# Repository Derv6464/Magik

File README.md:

# Magik - Flight Computer

This was built as a final year project for college, as well as to create a flight computer for ULAS HiPR.
The code and pcb are rough drafts with work to be done before the first flight. 

## Hardware
The code & pcb were created with a rp2040 chip in mind

## Report
Full report can be veiwed in the repo

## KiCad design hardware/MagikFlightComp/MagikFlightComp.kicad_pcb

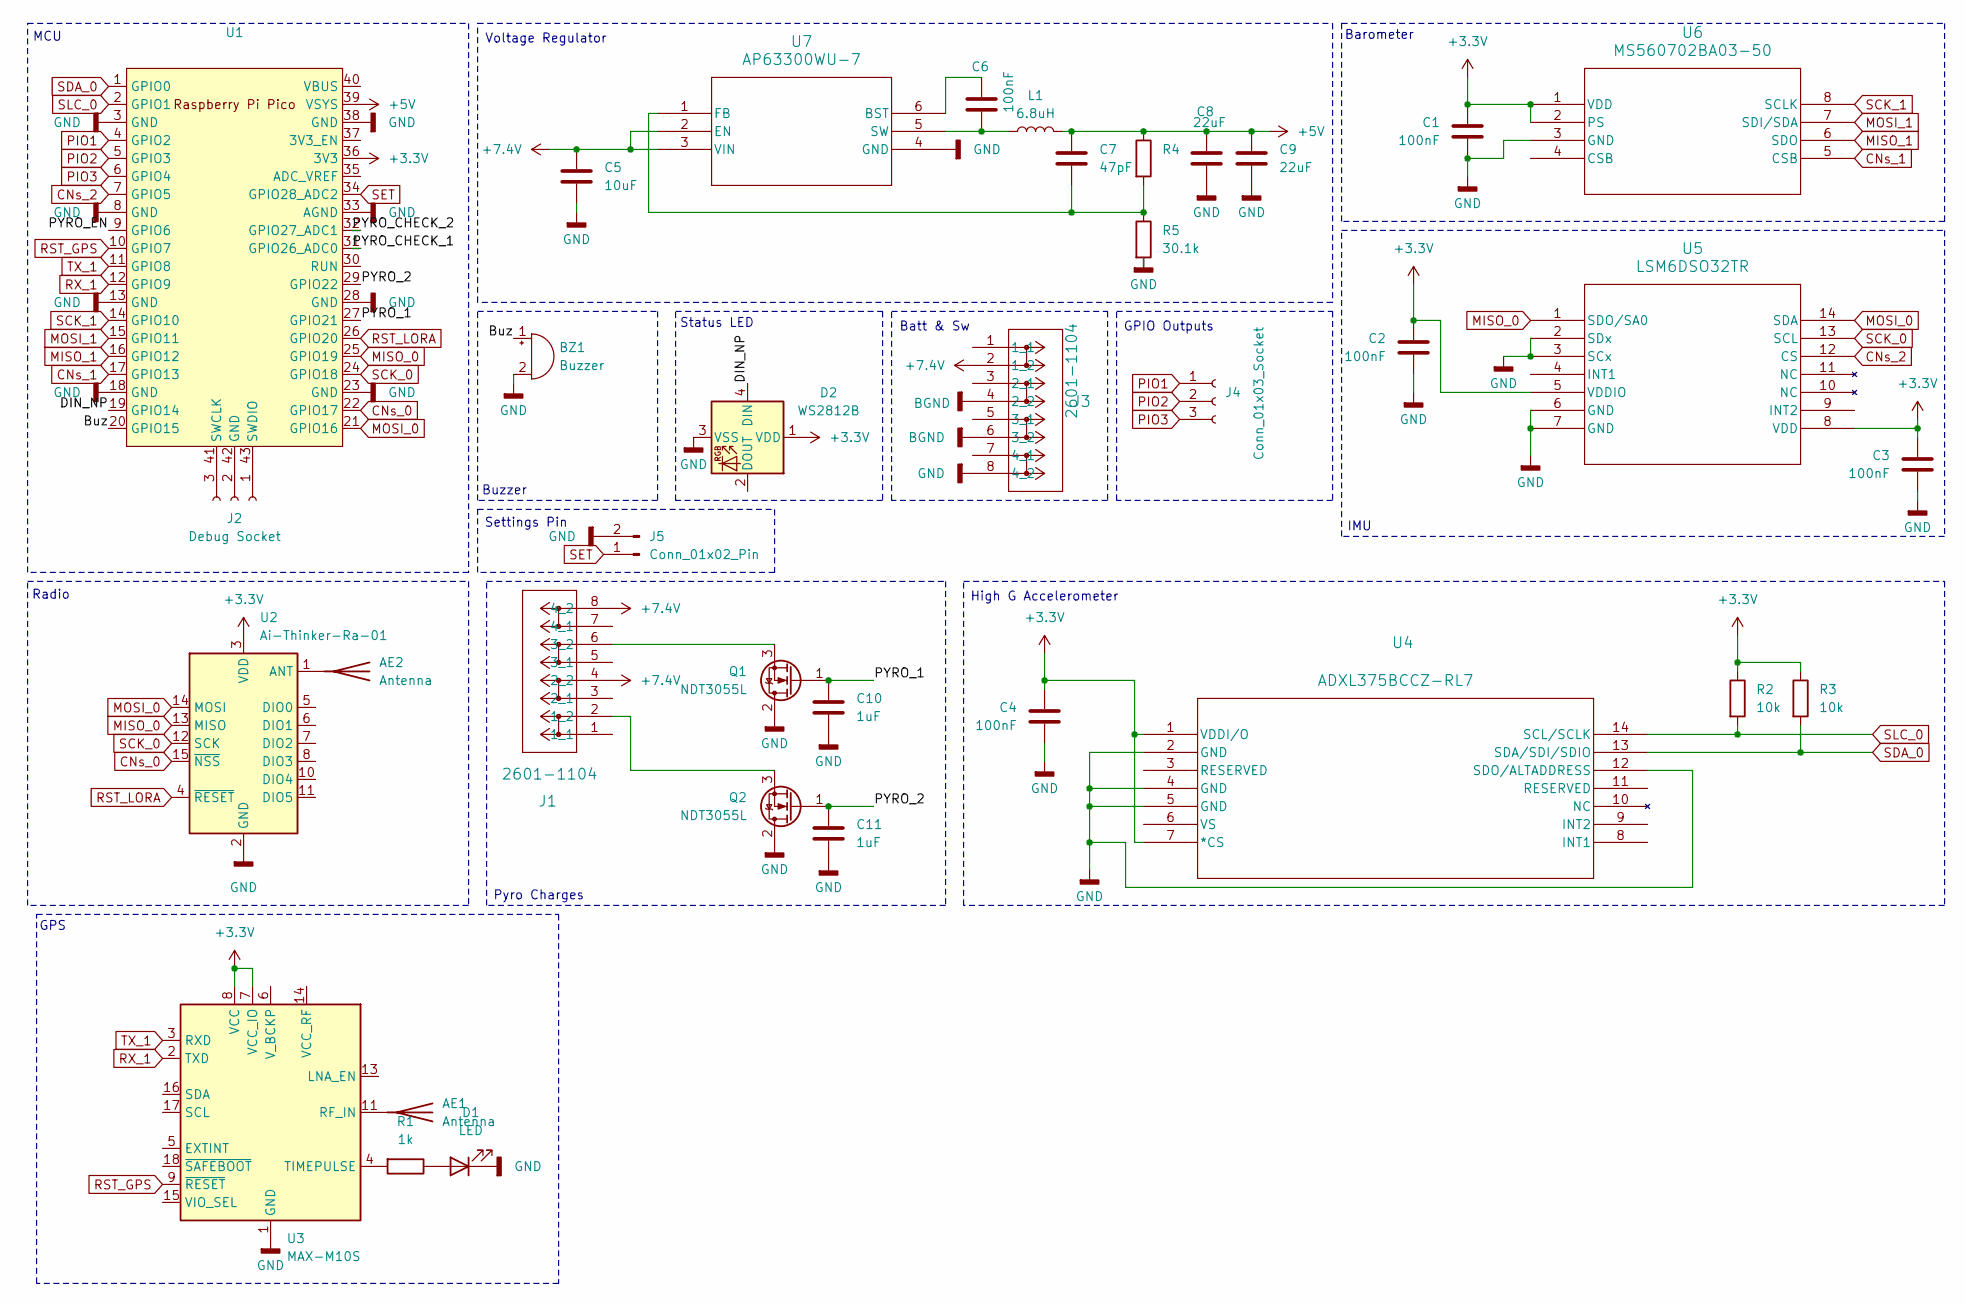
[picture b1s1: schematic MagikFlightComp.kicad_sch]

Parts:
AE1: Antenna
AE2: Antenna; SMA_Molex_73251-1153_EdgeMount_Horizontal
BZ1: Buzzer; Buzzer_12x9.5RM7.6
C1, C2, C3, C4, C6: 100nF; C_0603_1608Metric_Pad1.08x0.95mm_HandSolder
C5: 10uF; C_0603_1608Metric_Pad1.08x0.95mm_HandSolder
C7: 47pF; C_0603_1608Metric_Pad1.08x0.95mm_HandSolder
C8, C9: 22uF; C_0603_1608Metric_Pad1.08x0.95mm_HandSolder
C10, C11: 1uF; C_0603_1608Metric_Pad1.08x0.95mm_HandSolder
D1: LED; LED_1210_3225Metric
D2: WS2812B; LED_WS2812B_PLCC4_5.0x5.0mm_P3.2mm
J1, J3: 2601-1104; CONN4_2601-1104_WAG
J2: Debug Socket
J4: Conn_01x03_Socket; JST_PH_B3B-PH-K_1x03_P2.00mm_Vertical
J5: Conn_01x02_Pin; PinHeader_1x02_P1.00mm_Vertical
L1: 6.8uH; L_0603_1608Metric_Pad1.05x0.95mm_HandSolder
Q1, Q2: NDT3055L; SOT-223-3_TabPin2
R1: 1k; R_0603_1608Metric_Pad0.98x0.95mm_HandSolder
R2, R3: 10k; R_0603_1608Metric_Pad0.98x0.95mm_HandSolder
R4: 158k; R_0603_1608Metric_Pad0.98x0.95mm_HandSolder
R5: 30.1k; R_0603_1608Metric_Pad0.98x0.95mm_HandSolder
U1: Pico; RaspberryPi_Pico_W_SMD_HandSolder
U2: Ai-Thinker-Ra-01; Ai-Thinker-Ra-01-LoRa
U3: MAX-M10S; ublox_MAX
U4: ADXL375BCCZ-RL7; LGA_CC-14-1_ADI
U5: LSM6DSO32TR; LGA-14L_2P5X3X0P83_STM
U6: MS560702BA03-50; SON8_MS5611_TEC
U7: AP63300WU-7; TSOT6_AP63300WU-7_DIO

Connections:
+3.3V: C1.1, C2.1, C3.1, C4.1, D2.1 (VDD), R2.1, R3.1, U1.36 (3V3), U2.3 (VDD), U3.7 (VCC_IO), U3.8 (VCC), U4.1 (VDDI/O), U4.7 (*CS), U5.5 (VDDIO), U5.8 (VDD), U6.1 (VDD), U6.2 (PS)
+5V: C7.1, C8.1, C9.1, L1.2, R4.1, U1.39 (VSYS)
+7.4V: C5.1, J1.4 (2_2), J1.8 (4_2), J3.2 (1_2), U7.2 (EN), U7.3 (VIN)
/Buz: BZ1.1 (+), U1.20 (GPIO15)
/DIN_NP: D2.4 (DIN), U1.19 (GPIO14)
/PYRO_1: C10.1, Q1.1 (G), U1.27 (GPIO21)
/PYRO_2: C11.1, Q2.1 (G), U1.29 (GPIO22)
/PYRO_CHECK_1: U1.31 (GPIO26_ADC0)
/PYRO_CHECK_2: U1.32 (GPIO27_ADC1)
/PYRO_EN: U1.9 (GPIO6)
BGND: J3.4 (2_2), J3.6 (3_2)
CNs_0: U1.22 (GPIO17), U2.15 (~NSS)
CNs_1: U1.17 (GPIO13), U6.5 (CSB)
CNs_2: U1.7 (GPIO5), U5.12 (CS)
GND: BZ1.2 (-), C1.2, C2.2, C3.2, C4.2, C5.2, C8.2, C9.2, C10.2, C11.2, D1.1 (K), D2.3 (VSS), J3.8 (4_2), J5.2, Q1.2 (D), Q2.2 (D), R5.2, U1.3 (GND), U1.8 (GND), U1.13 (GND), U1.18 (GND), U1.23 (GND), U1.28 (GND), U1.33 (AGND), U1.38 (GND), U2.2 (GND), U2.9 (GND), U2.16 (GND), U3.1 (GND), U3.10 (GND), U3.12 (GND), U4.2 (GND), U4.4 (GND), U4.5 (GND), U4.12 (SDO/ALTADDRESS), U5.2 (SDx), U5.3 (SCx), U5.6 (GND), U5.7 (GND), U6.3 (GND), U7.4 (GND)
MISO_0: U1.25 (GPIO19), U2.13 (MISO), U5.1 (SDO/SA0)
MISO_1: U1.16 (GPIO12), U6.6 (SDO)
MOSI_0: U1.21 (GPIO16), U2.14 (MOSI), U5.14 (SDA)
MOSI_1: U1.15 (GPIO11), U6.7 (SDI/SDA)
unnamed: AE1.1, U3.11 (RF_IN)
unnamed: AE2.1 (A), U2.1 (ANT)
unnamed: D1.2 (A), R1.1
unnamed: J1.2 (1_2), Q2.3 (S)
unnamed: J1.6 (3_2), Q1.3 (S)
unnamed: J2.1, U1.43 (SWDIO)
unnamed: J2.2, U1.42 (GND)
unnamed: J2.3, U1.41 (SWCLK)
unnamed: R1.2, U3.4 (TIMEPULSE)
unnamed: C6.1, U7.6 (BST)
unnamed: C7.2, R4.2, R5.1, U7.1 (FB)
unnamed: C6.2, L1.1, U7.5 (SW)
PIO1: J4.1, U1.4 (GPIO2)
PIO2: J4.2, U1.5 (GPIO3)
PIO3: J4.3, U1.6 (GPIO4)
RST_GPS: U1.10 (GPIO7), U3.9 (~RESET)
RST_LORA: U1.26 (GPIO20), U2.4 (~RESET)
RX_1: U1.12 (GPIO9), U3.2 (TXD)
SCK_0: U1.24 (GPIO18), U2.12 (SCK), U5.13 (SCL)
SCK_1: U1.14 (GPIO10), U6.8 (SCLK)
SDA_0: R3.2, U1.1 (GPIO0), U4.13 (SDA/SDI/SDIO)
SET: J5.1, U1.34 (GPIO28_ADC2)
SLC_0: R2.2, U1.2 (GPIO1), U4.14 (SCL/SCLK)
TX_1: U1.11 (GPIO8), U3.3 (RXD)

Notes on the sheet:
Radio
Buzzer
Settings Pin
High G Accelerometer
Voltage Regulator
GPS
MCU
Status LED
IMU
Batt & Sw
GPIO Outputs
Pyro Charges
Barometer

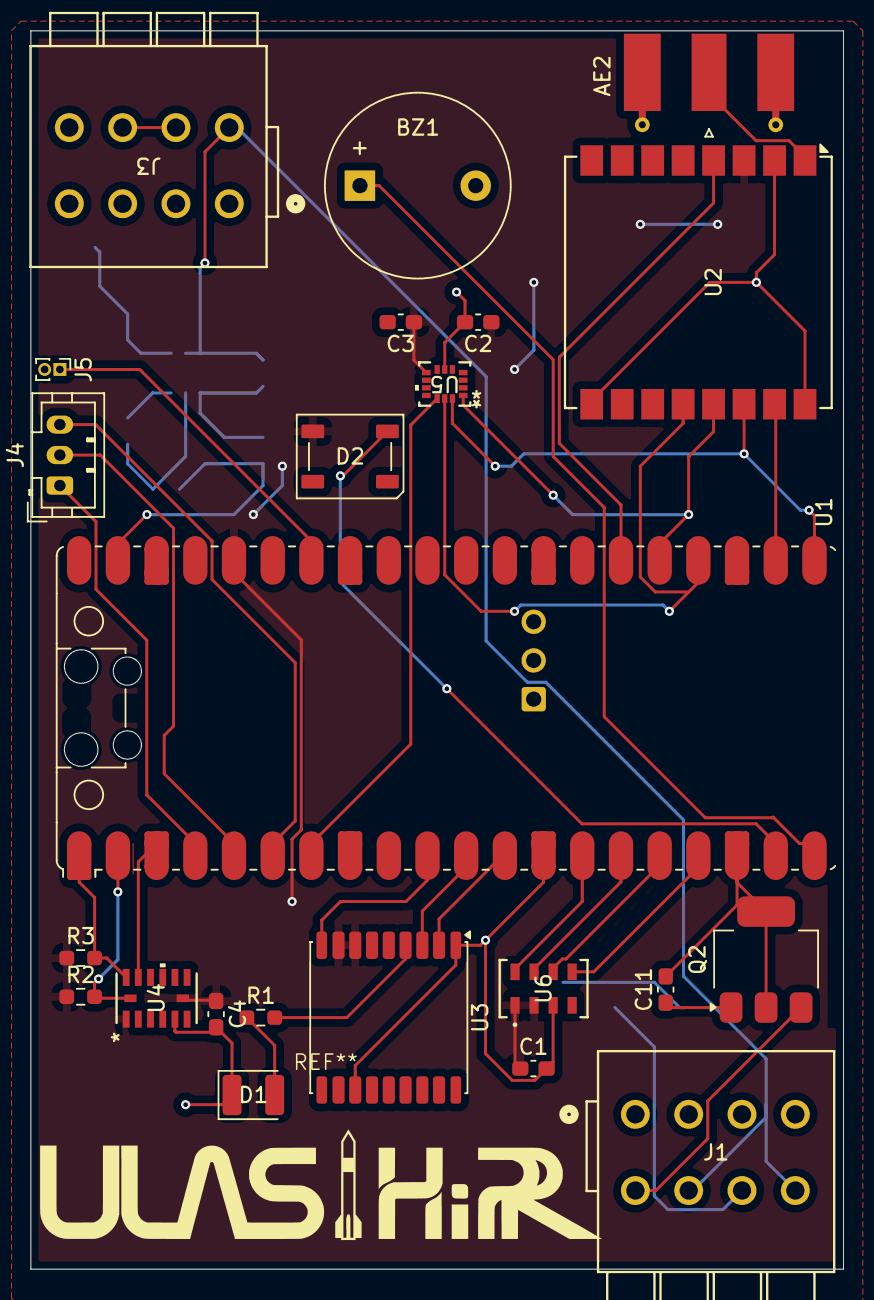
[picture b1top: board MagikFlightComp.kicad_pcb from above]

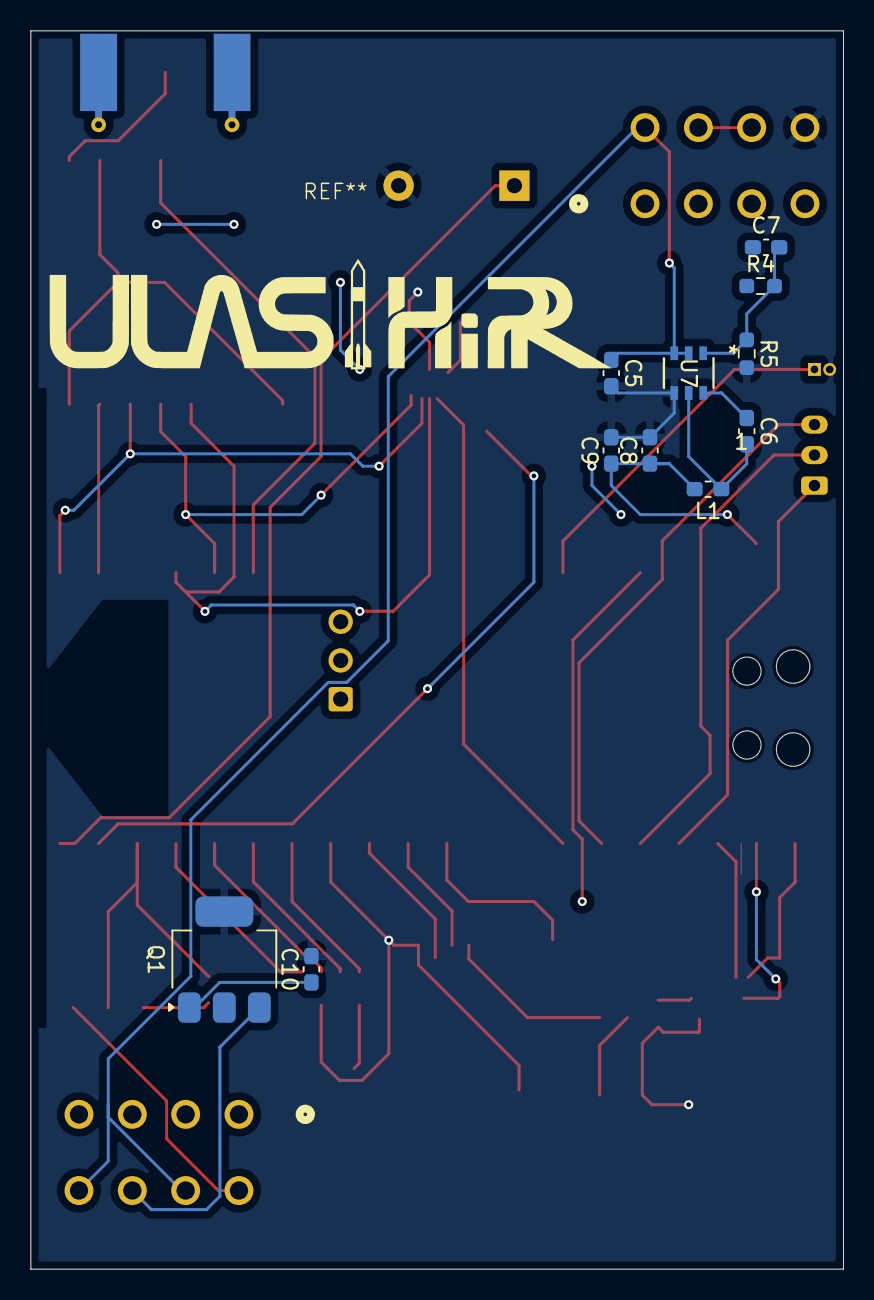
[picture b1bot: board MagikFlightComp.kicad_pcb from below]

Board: 2 copper layers, 53.3 x 81.3 mm, 34 parts (11 on the bottom side), 36 nets.

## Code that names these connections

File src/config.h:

#pragma once

//#define TESTING
#define TEST_RIG

#define read_data_delay 50 //ms 
#define send_data_delay 5000 //ms

//#define BARO_BMP390
//#define ACCEL_LSM6DS3
//#define ACCEL_ADXL345
#define ACCEL_MPU6050
//#define GPS_MAXM10S
//#define RADIO_SX1278
//#define LOG_SD

#ifdef TEST_RIG
#define BARO_BMP390
//#define ACCEL_LSM6DSOX
//#define GPS_PA
//#define RADIO_RM95W

#endif


#define LOG_INTERNAL_FLASH
#define LOG_FLASH_OFFSET 1024*1024 
#define SETTINGS_OFFSET 1024*512 

//I2C bus for high g accelerometer
//#define sda_0 0
//#define scl_0 1

//I2C bus for accelerometer
#define sda_0 4
#define scl_0 5

//SPI bus for barometer and low g accelerometer/IMU
#define sck_1 10
#define mosi_1 11
#define miso_1 12
#define cs_baro 13
#define cs_imu 5

//SPI bus for LoRa
#define sck_0 18
#define mosi_0 19
#define miso_0 16
#define cs_lora 17
#define rst_lora 20

#define neopixel 14
#define buzzer 15

//UART bus for GPS
//#define tx_1 8
//#define rx_1 9
#define rst_gps 7

#ifdef TESTING
//UART bus for testing
#define tx_1 8
#define rx_1 9

#endif

//Pyro channels
#define pyro_en 6
#define pyro_1 26
#define pyro_2 27
//#define pyro_check_1 26
//#define pyro_check_2 27

#define bt_setting_pin 2

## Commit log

2025-03-23 iit files
2025-03-23 status led be working :)
2025-03-27 Added bunch of files
2025-03-30 added sensor handling
2025-04-12 bunch of sensor and testing stuff
2025-04-14 stuff i forgot to commit from yesterday
2025-04-15 it actully works kinda ish
2025-04-15 mocking done (excetp timing but oh well
2025-04-15 other files for testing pico
2025-04-17 why has git broken
2025-04-19 fixing testing & state machine
2025-04-19 rejig files
2025-04-19 rejig files p2
2025-04-19 base telemetry
2025-04-19 telemetry runs, but doesnt work
2025-04-21 velocity working, logging questionable
2025-04-21 height working kinda
2025-04-21 forgot to add files AGAIN
2025-04-22 drivers for mpu6050 with i2c, and very base bt server class
2025-04-22 mpu working - hell yeah
2025-04-22 adding eigen module
2025-04-22 adding eigen module - forgot stuff
2025-04-22 stuff
2025-04-26 kalman done kinda, velocity no work
2025-04-27 oops
2025-04-28 kalman adjustmennts
2025-04-29 basic bt compiling, working??? who knows
2025-04-29 files
2025-05-04 results r fucked
2025-05-07 bt server, and starting gps driver
2025-05-08 idk anymore
2025-05-08 idk anymore p2
2025-05-09 settings work, hell yeah
2025-05-09 settings matter now
2025-05-12 final commit
2025-05-14 added pcb files
2025-05-14 removing old graphing stuff
2025-10-07 pushing final work
2025-10-07 Adding report & readme
